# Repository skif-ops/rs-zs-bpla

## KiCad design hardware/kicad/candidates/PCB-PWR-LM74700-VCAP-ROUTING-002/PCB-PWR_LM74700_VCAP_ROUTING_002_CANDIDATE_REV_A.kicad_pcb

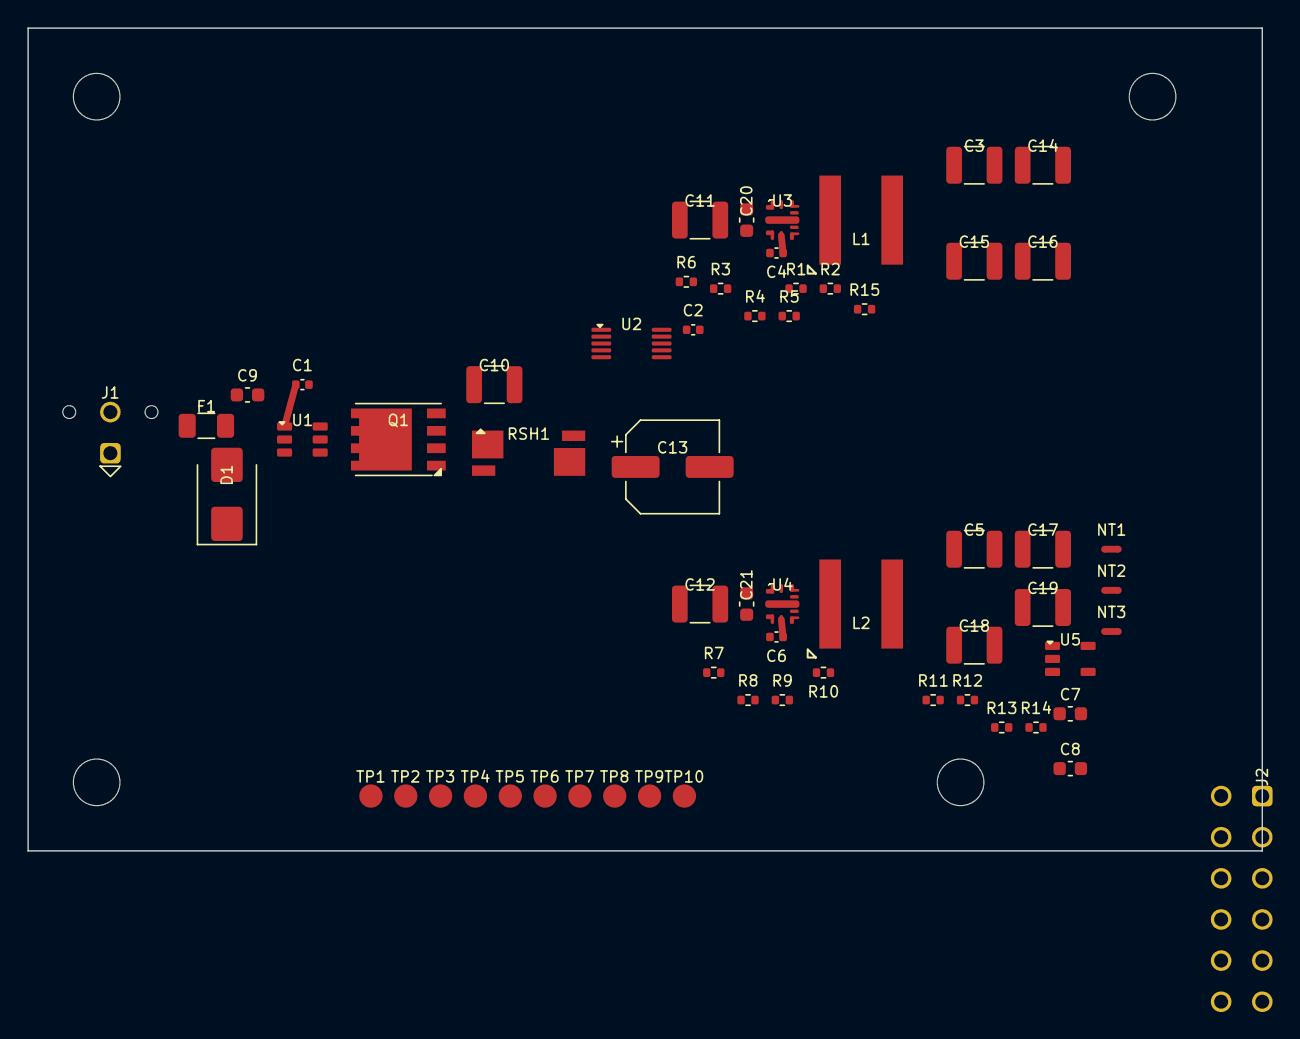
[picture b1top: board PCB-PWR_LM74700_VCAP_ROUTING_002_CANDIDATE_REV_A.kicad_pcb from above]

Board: 4 copper layers, 90.0 x 60.0 mm, 66 parts (0 on the bottom side), 31 nets.

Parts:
C1, C2, C4, C6: 100 nF 25 V X7R CGA2B3X7R1E104K050BB; C_0402_1005Metric
C3, C5, C14, C15, C16, C17, C18, C19: 22 uF 25 V X7R CGA6P3X7R1E226M250AB; C_1210_3225Metric
C7, C8: 2.2 uF 10 V X7R CGA3E1X7R1A225K080AC; C_0603_1608Metric
C9, C20, C21: 100 nF 50 V X7R CGA3E2X7R1H104K080AA; C_0603_1608Metric
C10, C11, C12: 4.7 uF 50 V X7R CGA6P3X7R1H475K250AB; C_1210_3225Metric
C13: 100 uF 35 V hybrid EEH-ZK1V101XP; CP_Elec_6.3x7.7
D1: SMBJ18A CANDIDATE; D_SMB
F1: 0451008.MRL; Fuse_1206_3216Metric
H1, H2, H3, H4: M3_CLEARANCE_NPTH_3.4; MountingHole_M3_3.4_EVT
J1: 43045-0213; Molex_43045-0213_MicroFit-2_Vertical
J2: 43045-1202; Molex_43045-1202_MicroFit-12_RA
L1, L2: XAL7030-472MEC; Coilcraft_XAL7030_472
NT1, NT2, NT3: 2-pad copper net tie NET_TIE_COPPER_REV_A; NetTie-2_SMD_Pad0.5mm
Q1: CSD18540Q5B; CSD18540Q5B_DNK
R1: 100 kOhm 0.1% ERA-2AEB104X; R_0402_1005Metric
R2: 35.7 kOhm 0.1% ERA-2AEB3572X; R_0402_1005Metric
R3, R7: 86.6 kOhm 0.1% ERA-2AEB8662X; R_0402_1005Metric
R4, R5, R8, R9: 0 ohm ERJ-2GE0R00X; R_0402_1005Metric
R6, R11: 100 kOhm 1% ERJ-2RKF1003X; R_0402_1005Metric
R10, R12, R15: 10 kOhm 1% ERJ-2RKF1002X; R_0402_1005Metric
R13, R14: 4.7 kOhm 1% ERJ-2RKF4701X; R_0402_1005Metric
RSH1: WSK2512R0100FEA; Vishay_WSK2512_4T_T1.19mm
TP1: TP_VBAT_PROTECTED DFT_PAD_1P70_NOPASTE_REV_A; TestPoint_DFT_1.7mm_NoPaste
TP2: TP_SHUNT_SRC DFT_PAD_1P70_NOPASTE_REV_A; TestPoint_DFT_1.7mm_NoPaste
TP3: TP_SHUNT_LOAD DFT_PAD_1P70_NOPASTE_REV_A; TestPoint_DFT_1.7mm_NoPaste
TP4: TP_3V8 DFT_PAD_1P70_NOPASTE_REV_A; TestPoint_DFT_1.7mm_NoPaste
TP5: TP_PG_3V8 DFT_PAD_1P70_NOPASTE_REV_A; TestPoint_DFT_1.7mm_NoPaste
TP6: TP_PWR_GOOD DFT_PAD_1P70_NOPASTE_REV_A; TestPoint_DFT_1.7mm_NoPaste
TP7: TP_1V8 DFT_PAD_1P70_NOPASTE_REV_A; TestPoint_DFT_1.7mm_NoPaste
TP8: TP_FAULT DFT_PAD_1P70_NOPASTE_REV_A; TestPoint_DFT_1.7mm_NoPaste
TP9: TP_SCL DFT_PAD_1P70_NOPASTE_REV_A; TestPoint_DFT_1.7mm_NoPaste
TP10: TP_SDA DFT_PAD_1P70_NOPASTE_REV_A; TestPoint_DFT_1.7mm_NoPaste
U1: LM74700QDBVRQ1; TI_DBV0006A_SOT23-6
U2: INA226AIDGSR; TI_DGS0010A_VSSOP10
U3, U4: LMR604403SRAKR; LMR60440_RAK0009A
U5: TPS7A2018PDBVR; TI_DBV0005A_SOT23-5

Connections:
1V8_MIC: C8.1, J2.5, TP7.1, U5.5
3V3_DIGITAL: C2.1, C5.1, C7.1, C17.1, C18.1, C19.1, J2.3, L2.2, R10.1, R12.1, R13.1, R14.1, R15.2, U2.6, U4.6, U5.1
3V8_MODEM: C3.1, C14.1, C15.1, C16.1, J2.1, L1.2, R1.1, TP4.1
BOOT_3V3: C6.1, U4.4
BOOT_3V8: C4.1, U3.4
EN_AUX: J2.10, R11.1, U5.3
EN_MODEM: J2.9, R6.1, U3.9
FAULT: J2.8, R12.2, TP8.1, U2.3
FB_3V8: R1.2, R2.1, U3.6
GND_DIGITAL: J2.4, NT2.1
GND_MIC: J2.6, NT3.1
GND_MODEM: J2.2, NT1.1
GND_PWR: C2.2, C3.2, C5.2, C7.2, C8.2, C9.2, C10.2, C11.2, C12.2, C13.2, C14.2, C15.2, C16.2, C17.2, C18.2, C19.2, C20.2, C21.2, D1.2, J1.2, NT1.2, NT2.2, NT3.2, R2.2, R3.2, R4.2, R6.2, R7.2, R8.2, R11.2, U1.2, U2.1, U2.2, U2.7, U3.2, U4.2, U5.2
I2C2_SCL: J2.11, R13.2, TP9.1, U2.5
I2C2_SDA: J2.12, R14.2, TP10.1, U2.4
LM74700_VCAP: C1.1, U1.1
MODE_3V3: R8.1, R9.1, U4.7
MODE_3V8: R4.1, R5.1, U3.7
PG_3V8: R15.1, TP5.1, U3.5
PWR_GOOD: J2.7, R10.2, TP6.1, U4.5
REV_GATE: Q1.4, U1.5
RT_3V3: R7.1, R9.2, U4.8
RT_3V8: R3.1, R5.2, U3.8
SHUNT_LOAD_SENSE: RSH1.4, TP3.1, U2.9
SHUNT_SOURCE_SENSE: RSH1.3, TP2.1, U2.10
SW_3V3: C6.2, L2.1, U4.3
SW_3V8: C4.2, L1.1, U3.3
VBAT_FUSED: C1.2, C9.1, D1.1, F1.2, Q1.1, Q1.2, Q1.3, U1.3, U1.6
VBAT_PROTECTED: C10.1, Q1.5, Q1.6, Q1.7, Q1.8, RSH1.1, TP1.1, U1.4
VBAT_RAW: F1.1, J1.1
VBAT_SYS: C11.1, C12.1, C13.1, C20.1, C21.1, RSH1.2, U2.8, U3.1, U4.1, U4.9

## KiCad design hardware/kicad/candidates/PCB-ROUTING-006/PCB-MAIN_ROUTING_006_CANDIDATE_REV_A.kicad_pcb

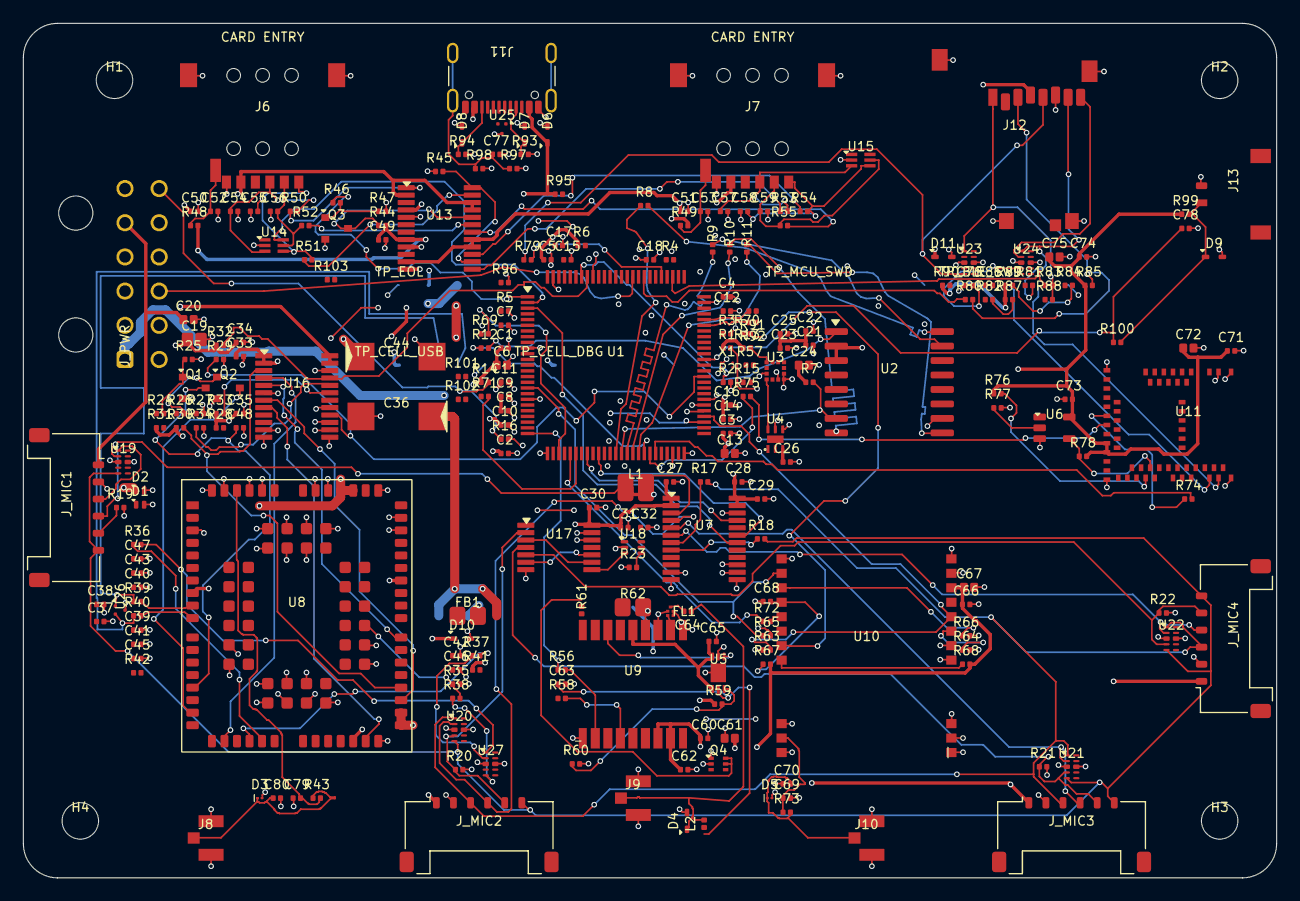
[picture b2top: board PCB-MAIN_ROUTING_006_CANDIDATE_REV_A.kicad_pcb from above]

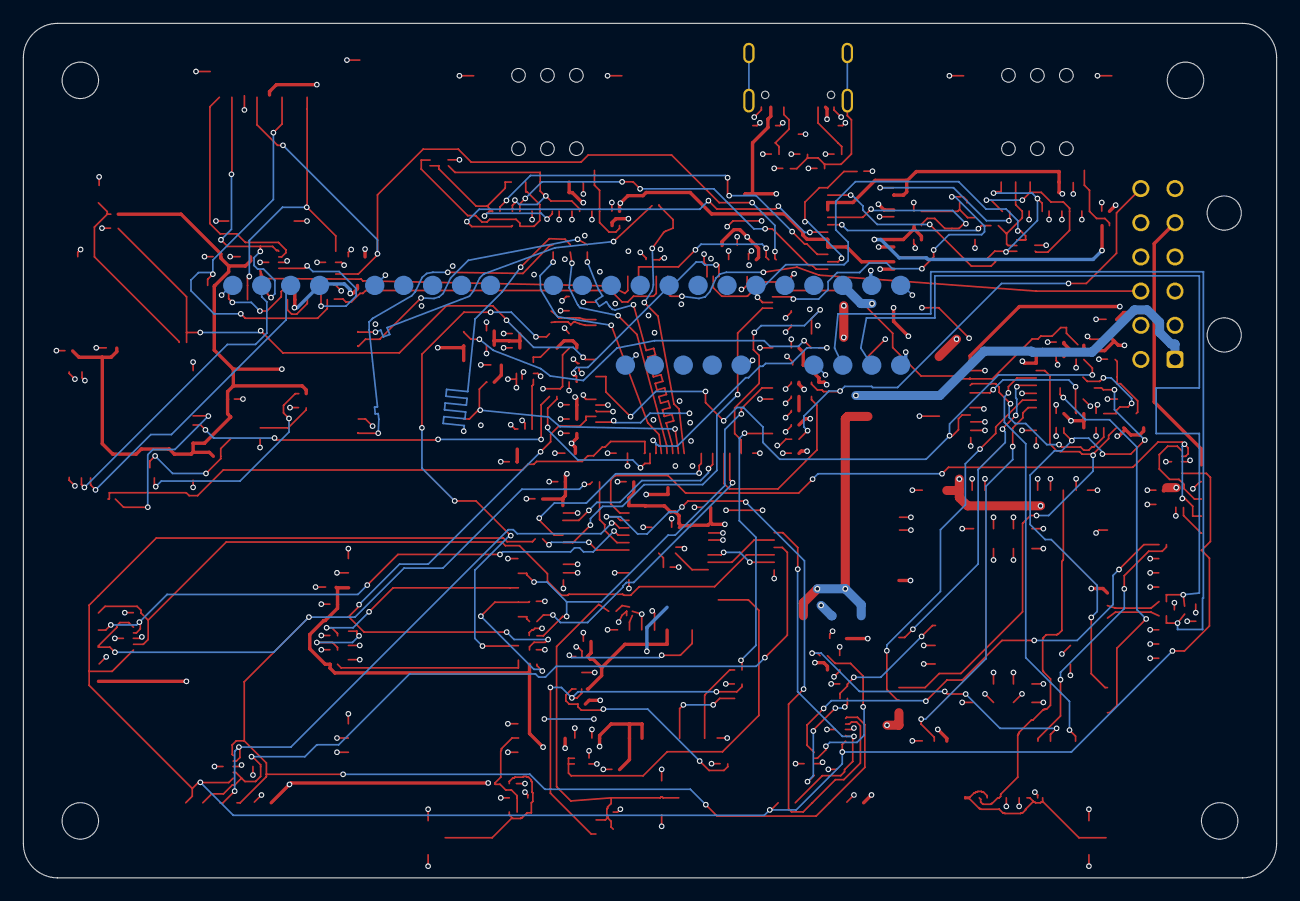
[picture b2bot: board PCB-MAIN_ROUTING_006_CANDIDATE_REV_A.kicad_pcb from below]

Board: 6 copper layers, 110.0 x 75.0 mm, 251 parts (5 on the bottom side), 186 nets.

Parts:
C1, C2, C3, C4, C5, C7, C8, C10, C12, C16, C17, C18, C21, C23, C25, C26, C27, C28, C29, C30, C31, C32, C33, C34, C35, C45, C49, C50, C51, C60, C62, C65, C66, C68, C71, C73, C74: GRM155R71E104KE14D
C6, C13, C20, C24, C61, C67, C72, C75: GRM188R61A106KE69D
C9, C11, C22: GRM155R61C105KA12D
C14, C15: GRM155R61A225KE15D
C19: GRM21BR61A226ME44L
C36, C44: T520D107M006ATE015; KEMET_T52X_D_7343-31_DensityB
C37: GRM155R71E224KE14D
C38: GRM155R71E473KA01D
C39: GRM1555C1H151JA01D
C40: GRM1555C1H101JA01D
C41: GRM1555C1H680JA01D
C42, C46, C54, C55, C56, C57, C58, C59: GRM1555C1H330JA01D
C43, C47, C69, C70, C79, C80: GRM1555C1H100JA01D
C48, C52, C53, C76, C78: GRM155R71E103KA01D
C63: GRM155R71C103KA01D
C64: GRM1555C1E470JA01D
C77: GRM155R72A472KA01D
D1, D2: PESD5V0S1UL; Nexperia_PESD5V0S1UL_SOD882
D3, D5: PESD5V0C1BSF; PESD5V0C1BSF_SOD962-2
D4, D6, D7, D8, D9, D10, D11: TPD1E05U06DYAR; TI_DYA0002A_SOD523
FB1: BLM31KN601SN1L
FL1: ABSES5AF-L100KM; Abracon_ABSES5AF_1109-5
H1, H2, H3, H4: M3_NPTH
J6, J7: 2336582-1; TE_2336582-1_NanoSIM
J8, J9, J10: U.FL-R-SMT-1(60); Hirose_U.FL-R-SMT-1
J11: USB4105-GF-A-120; USB_C_Receptacle_GCT_USB4105-xx-A_16P_TopMnt_Horizontal
J12: MEM2052-00-195-00-A; GCT_MEM2052-00-195-00-A
J13: 504050-0291; Molex_504050-0291_PicoLock-2
J_MIC1, J_MIC2, J_MIC3, J_MIC4: 504050-0691; Molex_Pico-Lock_504050-0691_1x06-1MP_P1.50mm_Horizontal
J_PWR: 43045-1202; Molex_43045-1202_MicroFit-12_RA
L1: LQH32PN2R2NN0L
L2: LQW15AN27NJ00D
Q1, Q2, Q3: MMBT3904,215; Nexperia_MMBT3904_SOT23
Q4: Si1016X-T1-GE3; Vishay_Si1016X_SC-89
R1, R7, R28, R30, R31, R46, R48, R49, R67, R68, R76, R78, R85, R86, R87, R88, R89, R90, R99: ERJ-2RKF1002X
R2, R3, R4, R5, R6, R19, R20, R21, R22, R23, R29, R32, R33, R34, R35, R45, R47, R63, R64, R65, R66, R77, R96: ERJ-2RKF1003X
R8, R9, R10, R11, R12, R15, R16, R17, R18, R36, R37, R56, R57, R58, R69, R70, R71, R72, R74, R75, R79, R80, R81, R82, R83, R84, R91, R92, R101: ERJ-2RKF22R0X
R13, R14: ERJ-2RKF2201X
R24, R26: ERJ-2RKF4701X
R25, R27, R44: ERJ-2RKF4702X
R38, R41, R95, R100, R102: ERJ-2RKF1001X
R39, R40, R42, R43, R50, R51, R52, R53, R54, R55, R73, R98, R103: ERJ-2GE0R00X
R59: ERJ-2GEJ561X
R60, R61: ERJ-2GEJ104X
R62: ERJ-8GEYJ100V
R93, R94: ERJ-2RKF5101X
R97: ERJ-2RKF1004X
TP_BLE_SWD: TEST_PADS
TP_CELL_DBG: TEST_PADS
TP_CELL_USB: TEST_PADS
TP_EOL: TEST_PADS
TP_MCU_SWD: TEST_PADS
U1: STM32U585VIT6Q; ST_STM32U585_LQFP100_1L
U2: W25Q512JVFIQ; Winbond_W25Q512JV_PackageF_IPC_Candidate
U3: LIS2DW12TR; ST_LIS2DW12_LGA-12L
U4: STTS22HTR; STTS22H_UDFN-6L
U5: LT6000IDCB#TRMPBF; LT6000_DCB-7
U6: SN74LVC1G07DBVR; TI_DBV0005A_SOT23-5
U7, U16: SN74AXC8T245PWR; TI_PW0024A_TSSOP24
U8: BG95-M3; Quectel_BG95-M3_LGA-102
U9: MAX-M10S-00B; u-blox_MAX-M10S_LCC-18
U10: E22-900M22S; Ebyte_E22-M22S_Castellated-22
U11: MDBT50Q-P1MV2; Raytac_MDBT50Q-P1MV2
U13: TS3A27518EPWR; TI_PW0024A_TSSOP24
U14, U15: ESDALC6V1-5P6; ST_ESDALC6V1-5P6_SOT666
U17: SN74LVC32APWR; TI_PW0014A_TSSOP14
U18: SN74AXC1T45DRLR; TI_DRL0006A_SOT6
U19, U20, U21, U22, U23, U24, U27: TPD4E05U06DQAR; TI_DQA0010A_USON10
U25, U26: TPD2EUSB30DRTR; TI_DRT0003A_IPC_Candidate
X1: SiT1552AI-JE-DCC-32.768D; SiT1552_JE_CSP-4

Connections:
1V8_MIC: C20.1, C27.1, C30.1, C31.1, J_MIC1.1, J_MIC2.1, J_MIC3.1, J_MIC4.1, J_PWR.5, TP_EOL.4, U7.1, U7.2, U17.14, U18.1, U18.5
3V3_DIGITAL: C1.1, C2.1, C3.1, C4.1, C5.1, C6.1, C7.1, C8.1, C9.1, C12.1, C13.1, C19.1, C21.1, C22.1, C23.1, C24.1, C25.1, C26.1, C28.1, C29.1, C32.1, C34.1, C35.1, C49.1, C60.1, C61.1, C62.1, C66.1, C67.1, C71.1, C72.1, C73.1, C74.1, C75.1, D11.1, J12.4, J_PWR.3, R1.1, R4.1, R6.1, R7.1, R13.1, R14.1, R28.1, R32.1, R33.1, R44.1, R48.1, R49.1, R67.1, R68.1, R76.1, R78.1, R85.1, R86.1, R87.1, R88.1, R89.1, R90.1, R99.1, TP_BLE_SWD.1, TP_EOL.2, TP_MCU_SWD.1, U1.6, U1.11, U1.20, U1.21, U1.27, U1.47, U1.51, U1.73, U1.75, U1.100, U2.2, U2.3, U3.2, U3.9, U3.10, U4.3, U6.5, U7.23, U7.24, U9.7, U9.8, U10.9, U11.28, U11.30, U13.8, U16.23, U16.24, U18.6, X1.3
3V8_MODEM: FB1.1, J_PWR.1, R42.1, TP_EOL.3
3V8_MODEM_BB: C36.1, C37.1, C38.1, C39.1, C40.1, C41.1, C42.1, C43.1, D1.1, FB1.2, U8.32, U8.33
3V8_MODEM_RF: C44.1, C45.1, C46.1, C47.1, D2.1, R42.2, U8.52, U8.53
AAD_CFG: U1.77, U7.16
AAD_CFG_1V8_FANOUT: J_MIC1.6, J_MIC2.6, J_MIC3.6, J_MIC4.6, R18.2, U19.5, U20.5, U21.5, U22.5
AAD_CFG_1V8_U7: R18.1, U7.8
ACCEL_INT: U1.63, U3.12
BLE_DFU_REQ: R76.2, U1.34, U11.39
BLE_EN: R77.1, U1.5, U6.2
BLE_RX_U1: R74.2, U1.45
BLE_RX_U11: R74.1, U11.22
BLE_TX_U1: R75.1, U1.44
BLE_TX_U11: R75.2, U11.24
BOOT0: R2.1, TP_EOL.9, U1.94
CELL_DBG_RXD_TP: R37.1, TP_CELL_DBG.3, U27.2
CELL_DBG_RXD_U8: R37.2, U8.22
CELL_DBG_TXD_TP: R36.2, TP_CELL_DBG.2, U27.1
CELL_DBG_TXD_U8: R36.1, U8.23
CELL_DBG_VREF_TP: R41.2, U27.4
CELL_DTR_U16: R29.1, U1.61, U16.16
CELL_PWRKEY_CMD: R24.1, U1.58
CELL_RESET_N_CMD: R26.1, U1.59
CELL_RF: C79.1, R43.1, U8.60
CELL_RF_ANT: C80.1, D3.1, J8.1, R43.2
CELL_RI_U16: R33.2, U1.62, U16.19
CELL_RX_U16: R32.2, U1.93, U16.21
CELL_STATUS_U16: R34.1, U1.60, U16.20
CELL_TX_U16: R28.2, U1.92, U16.17
CELL_USB_BOOT_1V8: R35.1, R38.2, U8.75
CELL_USB_BOOT_TP: R38.1, TP_CELL_DBG.4, U27.5
CELL_USB_DM_TP: R40.2, TP_CELL_USB.3, U26.2
CELL_USB_DM_U8: R40.1, U8.10
CELL_USB_DP_TP: R39.2, TP_CELL_USB.2, U26.1
CELL_USB_DP_U8: R39.1, U8.9
CELL_USB_VBUS: D10.1, TP_CELL_USB.1, U8.8
CELL_USIM_CLK_1V8: U8.46, U13.7
CELL_USIM_DATA_1V8: U8.45, U13.10
CELL_USIM_RST_1V8: U8.44, U13.6
CELL_USIM_VDD_1V8: U8.43, U13.4, U13.9, U13.12
EN_AUX: J_PWR.10, U1.86
EN_MODEM: J_PWR.9, U1.85
FAULT: J_PWR.8, R103.1, TP_EOL.8
GND_DIGITAL: C1.2, C2.2, C3.2, C4.2, C5.2, C6.2, C7.2, C8.2, C9.2, C10.2, C11.2, C12.2, C13.2, C14.2, C15.2, C16.2, C17.2, C18.2, C19.2, C21.2, C22.2, C23.2, C24.2, C25.2, C26.2, C27.2, C28.2, C29.2, C31.2, C32.2, C60.2, C61.2, C62.2, C63.2, C65.2, C66.2, C67.2, C68.2, C69.2, C70.2, C71.2, C72.2, C73.2, C74.2, C75.2, C76.2, C77.2, C78.2, D4.2, D5.2, D6.2, D7.2, D8.2, D9.2, D11.2, FL1.B, FL1.D, FL1.E, J9.SHIELD, J10.SHIELD, J11.A1, J11.A12, J11.B1, J11.B12, J12.6, J12.SHIELD, J13.2, J_PWR.4, Q4.1, R2.2, R3.2, R5.2, R23.2, R60.2, R63.2, R64.2, R65.2, R66.2, R77.2, R93.2, R94.2, R96.2, R97.2, R98.2, TP_BLE_SWD.4, TP_EOL.1, TP_MCU_SWD.5, U1.10, U1.19, U1.26, U1.48, U1.50, U1.74, U1.99, U2.10, U3.3, U3.6, U3.7, U3.8, U4.4, U4.5, U5.5, U5.EP, U6.3, U7.11, U7.12, U7.13, U7.14, U7.15, U7.22, U9.1, U9.10, U9.12, U10.1, U10.2, U10.3, U10.4, U10.5, U10.10, U10.11, U10.12, U10.20, U10.22, U11.1, U11.2, U11.15, U11.33, U11.55, U18.2, U23.3, U23.8, U24.3, U24.8, U25.3, X1.1, X1.4
GND_MIC: C20.2, C30.2, J_MIC1.2, J_MIC2.2, J_MIC3.2, J_MIC4.2, J_PWR.6, R19.2, R20.2, R21.2, R22.2, U17.7, U17.12, U17.13, U19.3, U19.8, U20.3, U20.8, U21.3, U21.8, U22.3, U22.8
GND_MODEM: C33.2, C34.2, C35.2, C36.2, C37.2, C38.2, C39.2, C40.2, C41.2, C42.2, C43.2, C44.2, C45.2, C46.2, C47.2, C48.2, C49.2, C50.2, C51.2, C52.2, C53.2, C54.2, C55.2, C56.2, C57.2, C58.2, C59.2, C79.2, C80.2, D1.2, D2.2, D3.2, D10.2, J6.4, J6.SHIELD, J7.4, J7.SHIELD, J8.SHIELD, J_PWR.2, Q1.2, Q2.2, Q3.2, R25.2, R27.2, R29.2, R34.2, R35.2, R45.2, R47.2, TP_CELL_DBG.5, TP_CELL_USB.4, U8.3, U8.31, U8.47, U8.48, U8.50, U8.54, U8.55, U8.58, U8.59, U8.61, U8.62, U8.67, U8.68, U8.69, U8.70, U8.71, U8.72, U8.73, U8.74, U8.79, U8.80, U8.81, U8.82, U8.89, U8.90, U8.91, U8.100, U8.101, U8.102, U13.5, U14.2, U15.2, U16.6, U16.11, U16.12, U16.13, U16.14, U16.15, U16.22, U26.3, U27.3, U27.8
GNSS_ANT_BIAS_RAW: C65.1, Q4.4, R61.1, U5.3, U5.4, U9.14
GNSS_ANT_DETECT: U5.6, U9.16
GNSS_ANT_DIV: R59.2, R60.1, U5.1
GNSS_ANT_GATE: Q4.5, Q4.6, R61.2
GNSS_ANT_OFF_N: Q4.2, U9.13
GNSS_ANT_SHORT_N: C63.1, L2.1, R62.2, U5.2, U9.17
GNSS_ANT_SWITCHED: Q4.3, R59.1, R62.1
GNSS_PPS_U1: R58.2, U1.22
GNSS_PPS_U9: R58.1, U9.4
GNSS_RF_ANT_BIASED: C64.1, D4.1, J9.1, L2.2
GNSS_RF_DC_BLOCK: C64.2, FL1.C
GNSS_RF_FILTERED: FL1.A, U9.11
GNSS_RX_U1: R56.2, U1.25
GNSS_RX_U9: R56.1, U9.2
GNSS_TX_U1: R57.1, U1.24
GNSS_TX_U9: R57.2, U9.3
HW_REV0: R3.1, R4.2
HW_REV1: R5.1, R6.2
I2C2_SCL_BUS: J_PWR.11, R13.2, R15.2, TP_EOL.12, U3.1, U4.1
I2C2_SCL_U1: R15.1, U1.52
I2C2_SDA_BUS: J_PWR.12, R14.2, R16.2, TP_EOL.13, U3.4, U4.6
I2C2_SDA_U1: R16.1, U1.53
LORA_BUSY: R66.1, U1.56, U10.14
LORA_DIO1: R65.1, U1.17, U10.13
LORA_MISO_U1: R72.2, U1.30
LORA_MISO_U10: R72.1, U10.16
LORA_MOSI_U1: R71.1, U1.31
LORA_MOSI_U10: R71.2, U10.17
LORA_NSS_U1: R69.1, U1.28
LORA_NSS_U10: R68.2, R69.2, U10.19
LORA_RESET_N: C68.1, R67.2, U1.57, U10.15
LORA_RF_ANT: C70.1, D5.1, J10.1, R73.2
LORA_RF_MODULE: C69.1, R73.1, U10.21
LORA_RXEN: R64.1, U1.55, U10.6
LORA_SCK_U1: R70.1, U1.29
LORA_SCK_U10: R70.2, U10.18
LORA_TXEN: R63.1, U1.54, U10.7
LSE_IN: U1.8, X1.2
MIC_WAKE: R23.1, U1.67, U18.4
MIC_WAKE1: J_MIC1.5, R19.1, U17.1, U19.4
MIC_WAKE2: J_MIC2.5, R20.1, U17.2, U20.4
MIC_WAKE3: J_MIC3.5, R21.1, U17.4, U21.4
MIC_WAKE4: J_MIC4.5, R22.1, U17.5, U22.4
MIC_WAKE12_OR_1V8: U17.3, U17.9
MIC_WAKE34_OR_1V8: U17.6, U17.10
MIC_WAKE_OR_1V8: U17.8, U18.3
NOR_CLK_U1: R8.1, U1.38
NOR_CLK_U2: R8.2, U2.16
NOR_IO0_U1: R9.1, U1.40
NOR_IO0_U2: R9.2, U2.15
NOR_IO1_U1: R10.1, U1.41
NOR_IO1_U2: R10.2, U2.8
NOR_IO2_U1: R11.1, U1.42
NOR_IO2_U2: R11.2, U2.9
NOR_IO3_U1: R12.1, U1.43
NOR_IO3_U2: R12.2, U2.1
NOR_NCS_U2: R7.2, U1.39, U2.7
NRF_RESET_N: R78.2, U6.4, U11.40
NRF_SWCLK: TP_BLE_SWD.3, U11.53
NRF_SWDIO: TP_BLE_SWD.2, U11.51
NRST: C18.1, R1.2, TP_MCU_SWD.4, U1.14
PDM_CLK: U1.37, U7.17
PDM_CLK_1V8_FANOUT: J_MIC1.3, J_MIC2.3, J_MIC3.3, J_MIC4.3, R17.2, U19.1, U20.1, U21.1, U22.1
PDM_CLK_1V8_U7: R17.1, U7.7
PDM_DATA1: U1.33, U7.21
PDM_DATA1_1V8: J_MIC1.4, U7.3, U19.2
PDM_DATA2: U1.87, U7.20
PDM_DATA2_1V8: J_MIC2.4, U7.4, U20.2
PDM_DATA3: U1.35, U7.19
PDM_DATA3_1V8: J_MIC3.4, U7.5, U21.2
PDM_DATA4: U1.3, U7.18
PDM_DATA4_1V8: J_MIC4.4, U7.6, U22.2
PWR_FAULT: R103.2, U1.82
PWR_GOOD: J_PWR.7, TP_EOL.7, U1.81
Q1_BASE: Q1.1, R24.2, R25.1
Q2_BASE: Q2.1, R26.2, R27.1
Q3_BASE: Q3.1, R46.2, R47.1
REV_STRAP0: TP_EOL.10, U1.95
REV_STRAP1: TP_EOL.11, U1.96
SD_CK_CARD: J12.5, R79.2, U23.5
SD_CK_U1: R79.1, U1.80
SD_CMD_CARD: J12.3, R80.2, R85.2, U23.4
SD_CMD_U1: R80.1, U1.83
SD_D0_CARD: J12.7, R81.2, R86.2, U24.1
SD_D0_U1: R81.1, U1.65
SD_D1_CARD: J12.8, R82.2, R87.2, U24.2
SD_D1_U1: R82.1, U1.66
SD_D2_CARD: J12.1, R83.2, R88.2, U23.1
SD_D2_U1: R83.1, U1.78
SD_D3_CARD: J12.2, R84.2, R89.2, U23.2
SD_D3_U1: R84.1, U1.79
SD_DET: C76.1, J12.CD, R90.2, U1.7, U24.4
SIM1_CLK_CONN: C55.1, J6.3, R51.2, U14.4
SIM1_CLK_MUX: R51.1, U13.23
SIM1_DATA_CONN: C56.1, J6.6, R52.2, U14.5
SIM1_DATA_MUX: R52.1, U13.19
SIM1_DET: C52.1, J6.7, R48.2, U1.2, U14.6
SIM1_RST_CONN: C54.1, J6.2, R50.2, U14.3
SIM1_RST_MUX: R50.1, U13.1
SIM1_VDD_CONN: C50.1, J6.1, U13.2, U13.21, U13.22, U14.1
SIM2_CLK_CONN: C58.1, J7.3, R54.2, U15.4
SIM2_CLK_MUX: R54.1, U13.15
SIM2_DATA_CONN: C59.1, J7.6, R55.2, U15.5
SIM2_DATA_MUX: R55.1, U13.18
SIM2_DET: C53.1, J7.7, R49.2, U1.4, U15.6
SIM2_RST_CONN: C57.1, J7.2, R53.2, U15.3
SIM2_RST_MUX: R53.1, U13.13
SIM2_VDD_CONN: C51.1, J7.1, U13.11, U13.16, U13.17, U15.1
SIM_MUX_EN: R46.1, U1.1
SIM_MUX_SEL: R45.1, U1.97, U13.14, U13.24
SMPS_SW: L1.1, U1.46
SWCLK: TP_MCU_SWD.3, U1.76
SWDIO: TP_MCU_SWD.2, U1.72
TAMPER_IN_CONN: D9.1, J13.1, R99.2, R100.1
TAMPER_IN_U1: C78.1, R100.2, U1.64
TEST_UART_RX_TP: R102.1, TP_EOL.6
TEST_UART_RX_U1: R102.2, U1.15
TEST_UART_TX_TP: R101.2, TP_EOL.5
TEST_UART_TX_U1: R101.1, U1.16
U8_MAIN_DTR_1V8: U8.30, U16.8
U8_MAIN_RI_1V8: R31.2, U8.39, U16.5
U8_MAIN_RXD_1V8: U8.34, U16.7
U8_MAIN_TXD_1V8: R30.2, U8.35, U16.3
U8_PWRKEY_N: C48.1, Q1.3, U8.15
U8_RESET_N: Q2.3, U8.17
U8_STATUS_1V8: U8.20, U16.4
U8_VDD_EXT_1V8: C33.1, R30.1, R31.1, R41.1, TP_CELL_DBG.1, U8.29, U16.1, U16.2
U13_EN_N: Q3.3, R44.2, U13.20
USB_CC1: D7.1, J11.A5, R93.1
USB_CC2: D8.1, J11.B5, R94.1
USB_DM_CONN: J11.A7, J11.B7, R92.2, U25.2
USB_DM_U1: R92.1, U1.70
USB_DP_CONN: J11.A6, J11.B6, R91.2, U25.1
USB_DP_U1: R91.1, U1.71
USB_SHIELD: C77.1, J11.SHIELD, R97.1, R98.1
USB_VBUS_CONN: D6.1, J11.A4, J11.A9, J11.B4, J11.B9, R95.1
USB_VBUS_SENSE: R95.2, R96.1, U1.68
VCORE_1V1: C14.1, C15.1, C16.1, C17.1, L1.2, U1.49, U1.98
VREF+: C10.1, C11.1
